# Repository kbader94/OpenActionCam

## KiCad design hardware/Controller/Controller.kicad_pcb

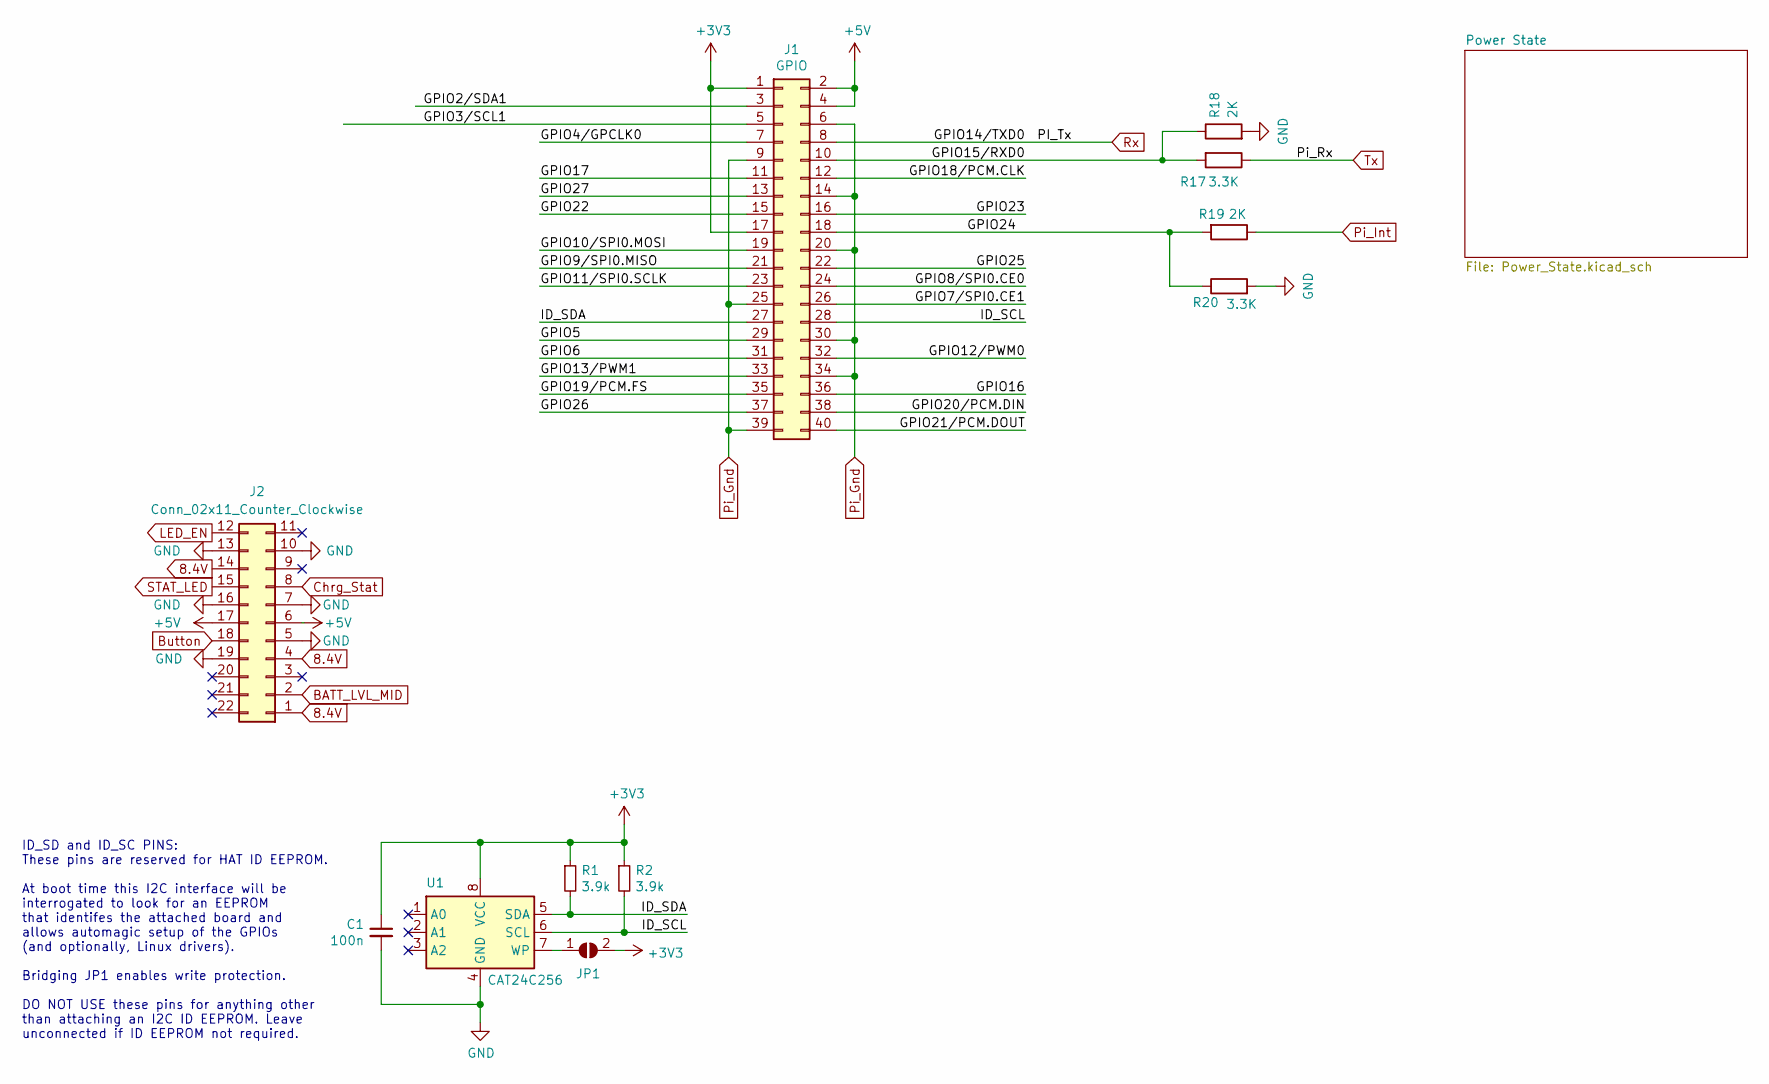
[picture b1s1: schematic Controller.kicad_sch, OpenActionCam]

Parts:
C1: 100n; C_0603_1608Metric_Pad1.08x0.95mm_HandSolder
J1: GPIO; Raspberry_Pi_Zero_Socketed_THT_FaceDown_MountingHoles
J2: Conn_02x11_Counter_Clockwise; Board_outline
JP1: ID_WP; SolderJumper-2_P1.3mm_Open_Pad1.0x1.5mm
R1, R2: 3.9k; R_0603_1608Metric_Pad0.98x0.95mm_HandSolder
R17, R20: 3.3K; R_0603_1608Metric_Pad0.98x0.95mm_HandSolder
R18, R19: 2K; R_0603_1608Metric_Pad0.98x0.95mm_HandSolder
U1: CAT24C256; SOIC127P600X175-8N

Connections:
8.4V: J2.1, J2.4, J2.14; also elsewhere on the board
+3V3: C1.1, J1.1, J1.17, JP1.2 (B), R1.1, R2.1, U1.8 (VCC)
+5V: J1.2, J1.4, J2.6, J2.17; also elsewhere on the board
/GPIO2/SDA1: J1.3
/GPIO3/SCL1: J1.5
/GPIO4/GPCLK0: J1.7
/GPIO5: J1.29
/GPIO6: J1.31
/GPIO7/SPI0.CE1: J1.26
/GPIO8/SPI0.CE0: J1.24
/GPIO9/SPI0.MISO: J1.21
/GPIO10/SPI0.MOSI: J1.19
/GPIO11/SPI0.SCLK: J1.23
/GPIO12/PWM0: J1.32
/GPIO13/PWM1: J1.33
/GPIO15/RXD0: J1.10, R17.2, R18.1
/GPIO16: J1.36
/GPIO17: J1.11
/GPIO18/PCM.CLK: J1.12
/GPIO19/PCM.FS: J1.35
/GPIO20/PCM.DIN: J1.38
/GPIO21/PCM.DOUT: J1.40
/GPIO22: J1.15
/GPIO23: J1.16
/GPIO24: J1.18, R19.1, R20.2
/GPIO25: J1.22
/GPIO26: J1.37
/GPIO27: J1.13
/ID_SCL: J1.28, R2.2, U1.6 (SCL)
/ID_SDA: J1.27, R1.2, U1.5 (SDA)
BATT_LVL_MID: J2.2; also elsewhere on the board
Button: J2.18; also elsewhere on the board
Chrg_Stat: J2.8; also elsewhere on the board
GND: C1.2, J2.5, J2.7, J2.10, J2.13, J2.16, J2.19, R18.2, R19.2, U1.4 (GND); also elsewhere on the board
LED_EN: J2.12; also elsewhere on the board
unnamed: JP1.1 (A), U1.7 (WP)
Pi_Gnd: J1.6, J1.9, J1.14, J1.20, J1.25, J1.30, J1.34, J1.39; also elsewhere on the board
Pi_Int: R20.1; also elsewhere on the board
Rx: J1.8; also elsewhere on the board
STAT_LED: J2.15; also elsewhere on the board
Tx: R17.1; also elsewhere on the board

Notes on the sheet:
ID_SD and ID_SC PINS: These pins are reserved for HAT ID EEPROM. At boot time this I2C interface will be interrogated to look for an EEPROM that identifes the attached board and allows automagic setup of the GPIOs (and optionally, Linux drivers). Bridging JP1 enables write protection. DO NOT USE th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

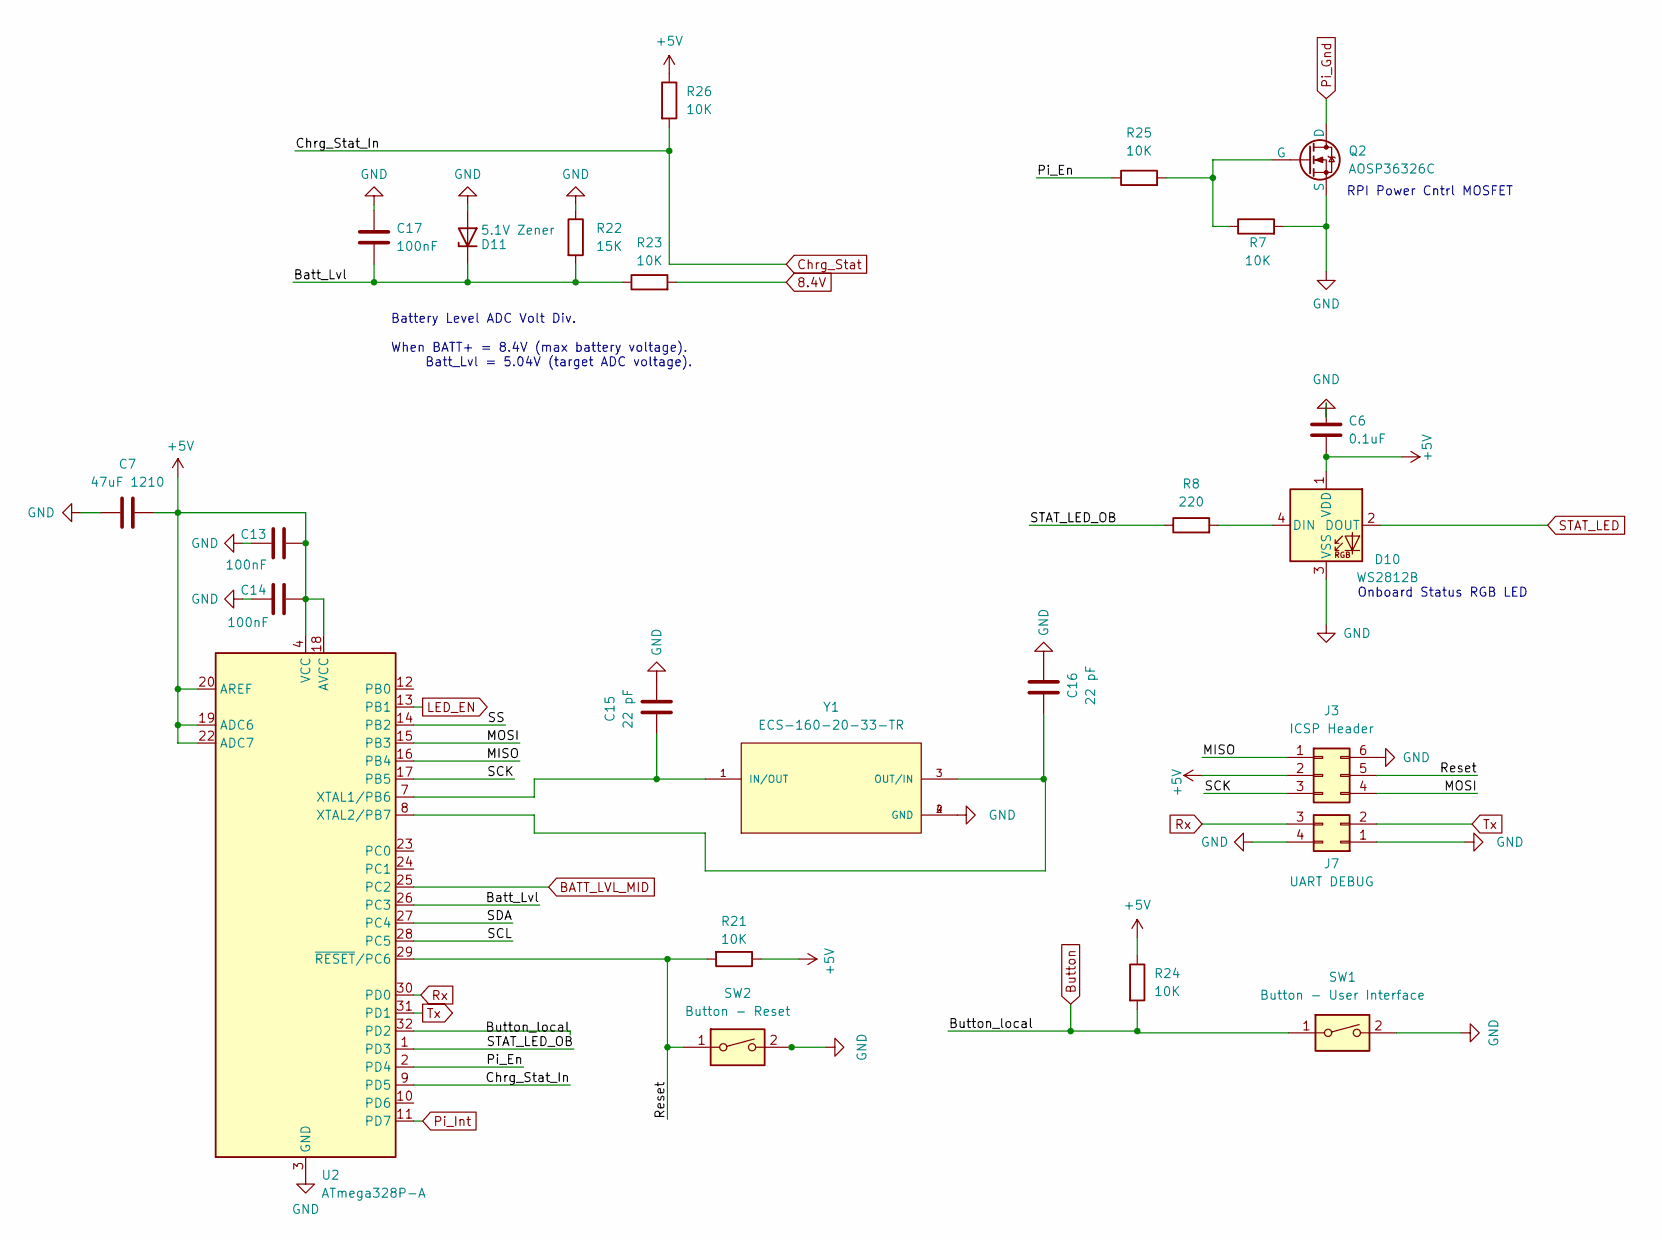
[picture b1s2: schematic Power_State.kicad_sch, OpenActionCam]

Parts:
C6: 0.1uF; C_0603_1608Metric_Pad1.08x0.95mm_HandSolder
C7: 47uF 1210; C_1210_3225Metric_Pad1.33x2.70mm_HandSolder
C13, C14, C17: 100nF; C_0603_1608Metric_Pad1.08x0.95mm_HandSolder
C15, C16: 22 pF; C_0603_1608Metric_Pad1.08x0.95mm_HandSolder
D10: WS2812B; LED_WS2812B_PLCC4_5.0x5.0mm_P3.2mm
D11: 5.1V Zener; D_SOD-323_HandSoldering
J3: ICSP Header; PinSocket_2x03_P2.54mm_Vertical
J7: UART DEBUG; PinSocket_2x02_P2.54mm_Vertical
Q2: AOSP36326C; SOIC127P490X600X175-8N
R7, R21, R23, R24: 10K; R_0603_1608Metric_Pad0.98x0.95mm_HandSolder
R8: 220; R_0603_1608Metric_Pad0.98x0.95mm_HandSolder
R22: 15K; R_0603_1608Metric_Pad0.98x0.95mm_HandSolder
R25, R26: 10K; R_0603_1608Metric
SW1: Button - User Interface; SW4_PTS815 SJM 250 SMTR LFS_CNK
SW2: Button - Reset; SW4_PTS815 SJM 250 SMTR LFS_CNK
U2: ATmega328P-A; TQFP-32_7x7mm_P0.8mm
Y1: ECS-160-20-33-TR; XTAL_ECS-160-20-33-TR

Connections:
8.4V: R23.2; also elsewhere on the board
+5V: C6.2, C7.2, C13.2, C14.2, D10.1 (VDD), J3.2, R21.1, R24.1, R26.1, U2.4 (VCC), U2.6 (VCC), U2.18 (AVCC), U2.19 (ADC6), U2.20 (AREF), U2.22 (ADC7); also elsewhere on the board
/Power State/Batt_Lvl: C17.2, D11.1 (K), R22.2, R23.1, U2.26 (PC3)
/Power State/MISO: J3.1, U2.16 (PB4)
/Power State/MOSI: J3.4, U2.15 (PB3)
/Power State/Pi_En: R25.1, U2.2 (PD4)
/Power State/Reset: J3.5, R21.2, SW2.1, U2.29 (~RESET/PC6)
/Power State/SCK: J3.3, U2.17 (PB5)
/Power State/SCL: U2.28 (PC5)
/Power State/SDA: U2.27 (PC4)
/Power State/SS: U2.14 (PB2)
/Power State/STAT_LED_OB: R8.1, U2.1 (PD3)
BATT_LVL_MID: U2.25 (PC2); also elsewhere on the board
Button: R24.2, SW1.1, U2.32 (PD2); also elsewhere on the board
Chrg_Stat: R26.2, U2.9 (PD5); also elsewhere on the board
GND: C6.1, C7.1, C13.1, C14.1, C15.2, C16.2, C17.1, D10.3 (VSS), D11.2 (A), J3.6, J7.1, J7.4, Q2.3 (S), R7.2, R22.1, SW1.2, SW2.2, U2.3 (GND), U2.5 (GND), U2.21 (GND), Y1.2 (GND), Y1.4 (GND); also elsewhere on the board
LED_EN: U2.13 (PB1); also elsewhere on the board
unnamed: D10.4 (DIN), R8.2
unnamed: Q2.2 (G), R7.1, R25.2
unnamed: C15.1, U2.7 (XTAL1/PB6), Y1.1 (IN/OUT)
unnamed: C16.1, U2.8 (XTAL2/PB7), Y1.3 (OUT/IN)
Pi_Gnd: Q2.1 (D); also elsewhere on the board
Pi_Int: U2.11 (PD7); also elsewhere on the board
Rx: J7.3, U2.30 (PD0); also elsewhere on the board
STAT_LED: D10.2 (DOUT); also elsewhere on the board
Tx: J7.2, U2.31 (PD1); also elsewhere on the board

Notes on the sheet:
Onboard Status RGB LED
RPI Power Cntrl MOSFET
Battery Level ADC Volt Div. When BATT+ = 8.4V (max battery voltage). Batt_Lvl = 5.04V (target ADC voltage).

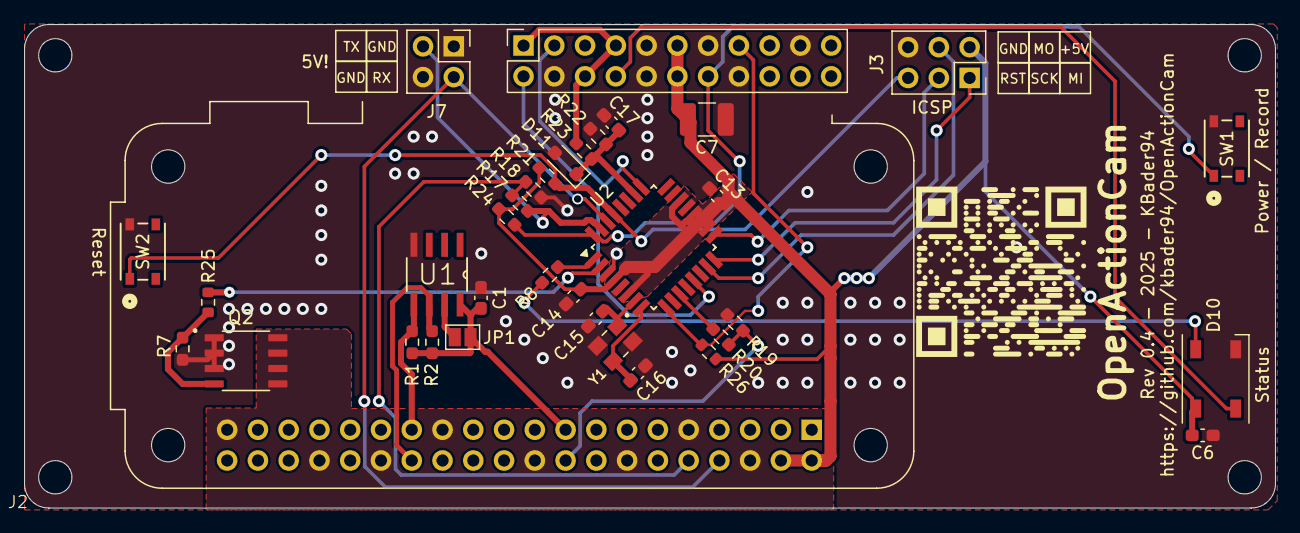
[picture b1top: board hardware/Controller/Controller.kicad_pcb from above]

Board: 2 copper layers, 103.3 x 39.9 mm, 35 parts (1 on the bottom side), 29 nets.

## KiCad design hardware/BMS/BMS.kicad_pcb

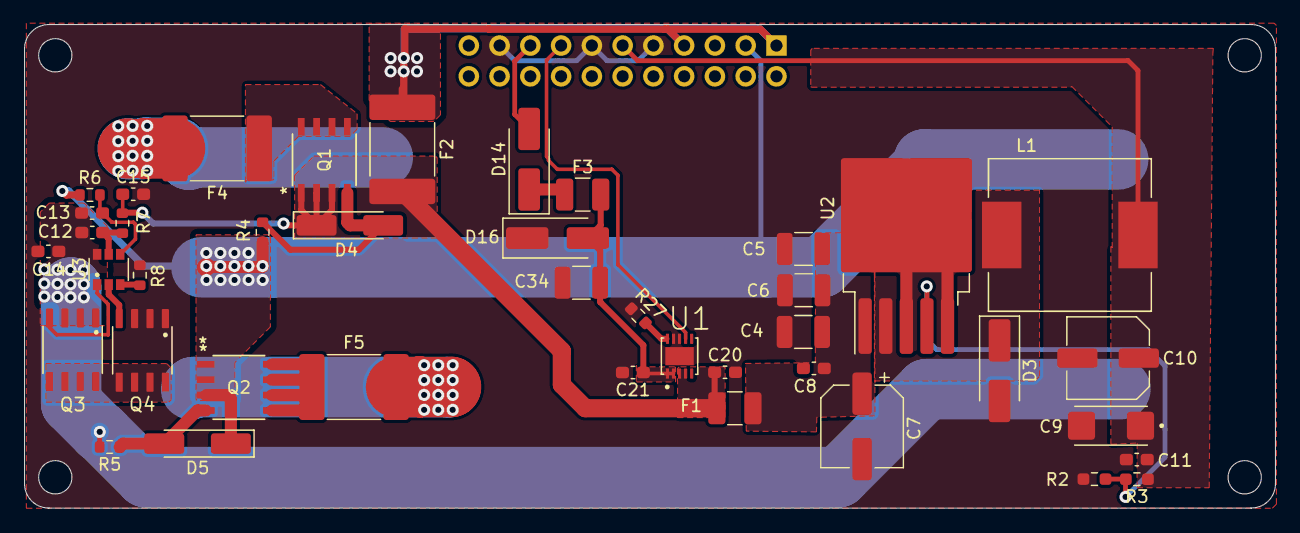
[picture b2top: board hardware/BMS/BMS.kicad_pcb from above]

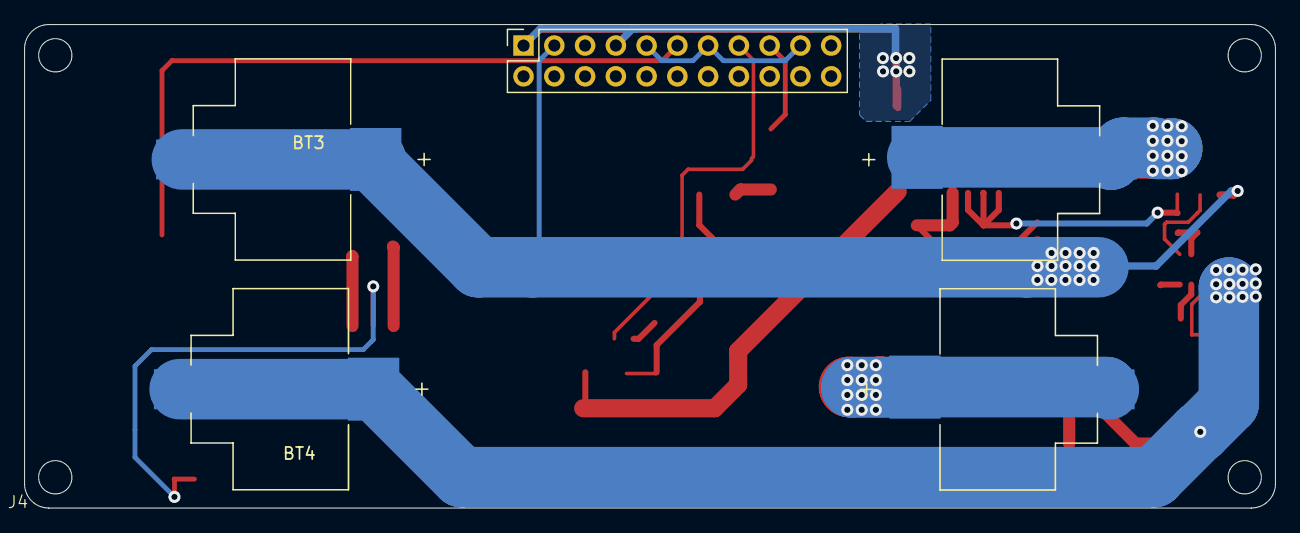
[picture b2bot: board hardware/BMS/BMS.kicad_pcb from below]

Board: 2 copper layers, 103.3 x 39.9 mm, 44 parts (3 on the bottom side), 26 nets.

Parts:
BT3, BT4: Battery_Cell; BAT_254
C4, C5, C6, C34: 47uF; R_1210_3225Metric_Pad1.30x2.65mm_HandSolder
C7: 100uF 16V; CP_Elec_6.3x7.7
C8, C11, C12, C14, C15: 0.1uF; C_0603_1608Metric_Pad1.08x0.95mm_HandSolder
C9: 330uF Tantalum; CAPPM6032X280N
C10: 330uF 10V; C_Elec_6.3x7.7
C13: 0.1 uF; C_0603_1608Metric_Pad1.08x0.95mm_HandSolder
C20, C21: 10uF; C_0603_1608Metric_Pad1.08x0.95mm_HandSolder
D3: SS34; D_SMA_Handsoldering
D4, D5: 9.1V Zener; D_MiniMELF_Handsoldering
D14: SS24; D_SMA_Handsoldering
D16: SMAJ11A; D_SMA_Handsoldering
F1, F3: 2.2A Polyfuse; Fuse_1210_3225Metric_Pad1.42x2.65mm_HandSolder
F2: 6A Polyfuse; Fuse_2920_7451Metric_Pad2.10x5.45mm_HandSolder
F4, F5: Polyfuse 6A; Fuse_2920_7451Metric_Pad2.10x5.45mm_HandSolder
J4: Conn_01x11; Board_outline
L1: 33uH; IND_125CDMCCDS-330MC
Q1, Q2: SI4435FDY; SO-8_VIS
Q3, Q4: AOSP36326C; SOIC127P490X600X175-8N
R2: 1K; R_0603_1608Metric_Pad0.98x0.95mm_HandSolder
R3: 3.1K; R_0603_1608Metric_Pad0.98x0.95mm_HandSolder
R4, R5: 100K; R_0603_1608Metric
R6, R7: 330; R_0603_1608Metric
R8: 2.2K; R_0603_1608Metric
R27: 1K; R_0603_1608Metric
U1: MCP73213-A6SI_MF; SON50P300X300X100-11N
U2: LM2596S-ADJ; TO-263-5_TabPin3
U3: MM3220AA2NRH; IC_MM3220AA2NRH

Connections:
8.4V: C15.1, C20.1, D4.1 (K), F1.1, F2.2, Q1.3 (S), R7.2, U1.3 (VBAT), U1.4 (VBAT)
+5V: C9.1, C10.1, C11.1, J4.6, L1.2, R3.1
+12V: C21.1, C34.2, D16.2 (A2), F3.2, U1.1 (VDD), U1.2 (VDD)
/Power BMS/8.4V Out: F2.1, J4.1, J4.4
/Power BMS/Battery Pack & Protection/8.4unsafe: F4.1, Q1.1 (D)
/Power BMS/Battery Pack & Protection/d2d: Q3.1 (D), Q4.1 (D)
/Power BMS/Power Supply/V_Out_Dirty: D3.1 (K), L1.1, U2.2 (OUT)
/Power BMS/Power Supply/Vin_clean: C4.1, C5.1, C6.1, C7.1, C8.1, F1.2, U2.1 (VIN)
BATT_LVL-: BT4.2 (-), C12.1, C13.2, C14.2, Q3.3 (S), R5.2, U3.6 (VSS)
BATT_LVL_MID: BT3.2 (-), D5.1 (K), J4.2, Q2.3 (S), R4.2, R6.1
Chrg_Stat: J4.8, U1.7 (STAT)
GND: C4.2, C5.2, C6.2, C7.2, C8.2, C9.2, C10.2, C11.2, C14.1, C15.2, C20.2, C21.2, C34.1, D3.2 (A), D16.1 (A1), J4.5, J4.7, J4.10, Q4.3 (S), R2.1, R8.2, R27.1, U1.8 (VSS), U1.9 (VSS), U1.11 (EP), U2.3 (GND), U2.5 (~ON/OFF)
unnamed: BT3.1 (+), F4.2
unnamed: BT4.1 (+), F5.2
unnamed: D4.2 (A), Q1.2 (G), R4.1
unnamed: D5.2 (A), Q2.2 (G), R5.1
unnamed: D14.2 (A), J4.9
unnamed: D14.1 (K), F3.1
unnamed: F5.1, Q2.1 (D)
unnamed: Q3.2 (G), U3.1 (DOUT)
unnamed: Q4.2 (G), U3.2 (COUT)
unnamed: R27.2, U1.10 (PROG)
unnamed: R2.2, R3.2, U2.4 (FB)
unnamed: R8.1, U3.3 (V-)
unnamed: C13.1, R6.2, U3.4 (VBL)
unnamed: C12.2, R7.1, U3.5 (VDD)

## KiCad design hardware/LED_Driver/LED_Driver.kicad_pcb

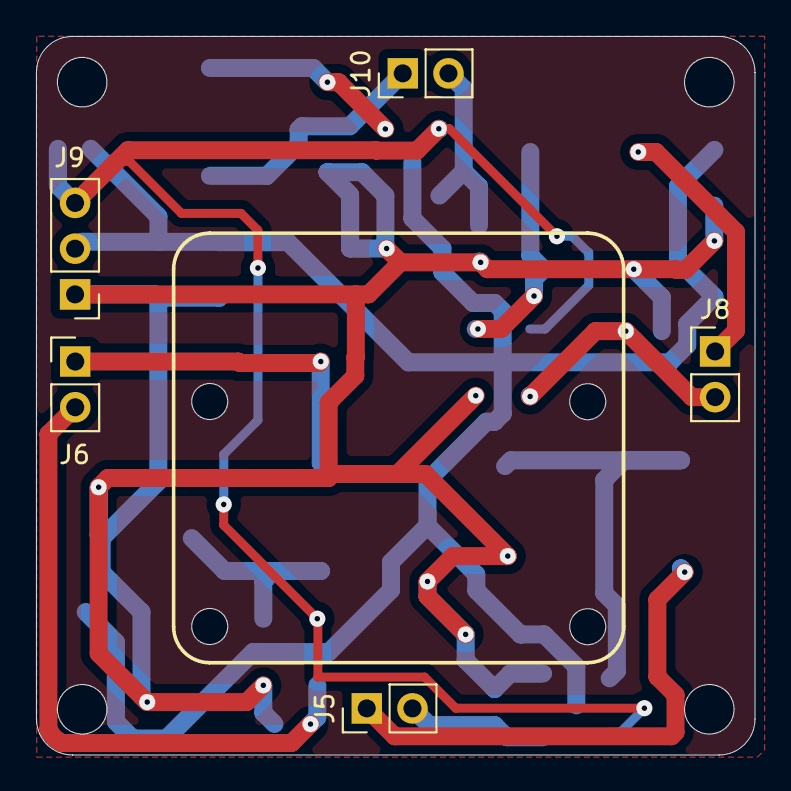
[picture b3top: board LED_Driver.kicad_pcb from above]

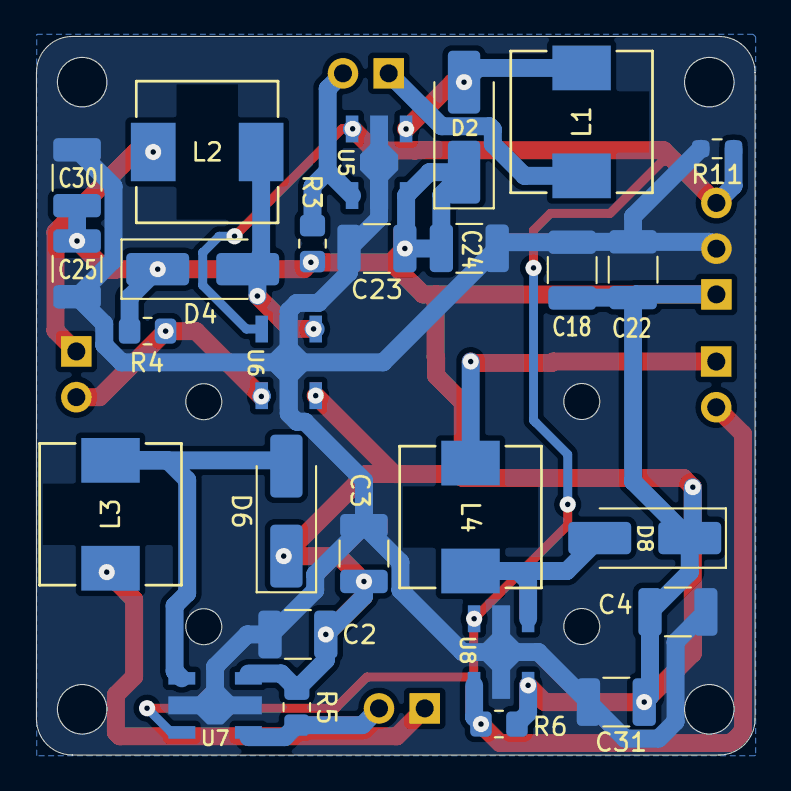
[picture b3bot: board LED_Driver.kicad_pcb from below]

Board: 2 copper layers, 39.9 x 39.9 mm, 32 parts (27 on the bottom side), 15 nets.

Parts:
C2, C3, C4, C18, C22, C23, C24, C25, C30, C31: 47uF 1210; R_1210_3225Metric_Pad1.30x2.65mm_HandSolder
D2, D4, D6, D8: SS14; D_SMA_Handsoldering
J5, J8, J9, J10: Conn_01x02_Pin; PinHeader_1x02_P2.54mm_Vertical
J6: Conn_01x03; PinHeader_1x03_P2.54mm_Vertical
L1, L2, L3, L4: 68 uH; DR74
R3: 0.15 - 0805; R_0805_2012Metric_Pad1.20x1.40mm_HandSolder
R4: 0.15 -0805; R_0805_2012Metric_Pad1.20x1.40mm_HandSolder
R5, R6: 0.15; R_0805_2012Metric_Pad1.20x1.40mm_HandSolder
R11: 10K; R_0603_1608Metric_Pad0.98x0.95mm_HandSolder
U5, U6, U7, U8: PT4115; SOT-89-5

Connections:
8.4V: C2.1, C3.1, C4.1, C18.1, C22.1, C23.1, C24.1, C25.1, C30.1, C31.1, D2.1 (K), D4.1 (K), D6.1 (K), D8.1 (K), J6.1, R3.1, R4.1, R5.1, R6.1, U5.5 (VIN), U6.5 (VIN), U7.5 (VIN), U8.5 (VIN)
GND: C2.2, C3.2, C4.2, C18.2, C22.2, C23.2, C24.2, C25.2, C30.2, C31.2, J6.2, R11.2, U5.2 (GND), U6.2 (GND), U7.2 (GND), U8.2 (GND)
LED_EN: J6.3, R11.1, U5.3 (DIM), U6.3 (DIM), U7.3 (DIM), U8.3 (DIM)
unnamed: D2.2 (A), L1.2, U5.1 (SW)
unnamed: D4.2 (A), L2.2, U6.1 (SW)
unnamed: D6.2 (A), L3.2, U7.1 (SW)
unnamed: D8.2 (A), L4.2, U8.1 (SW)
unnamed: J5.1, L3.1
unnamed: J5.2, R5.2, U7.4 (CSN)
unnamed: J8.1, L2.1
unnamed: J8.2, R4.2, U6.4 (CSN)
unnamed: J9.1, L4.1
unnamed: J9.2, R6.2, U8.4 (CSN)
unnamed: J10.1, L1.1
unnamed: J10.2, R3.2, U5.4 (CSN)

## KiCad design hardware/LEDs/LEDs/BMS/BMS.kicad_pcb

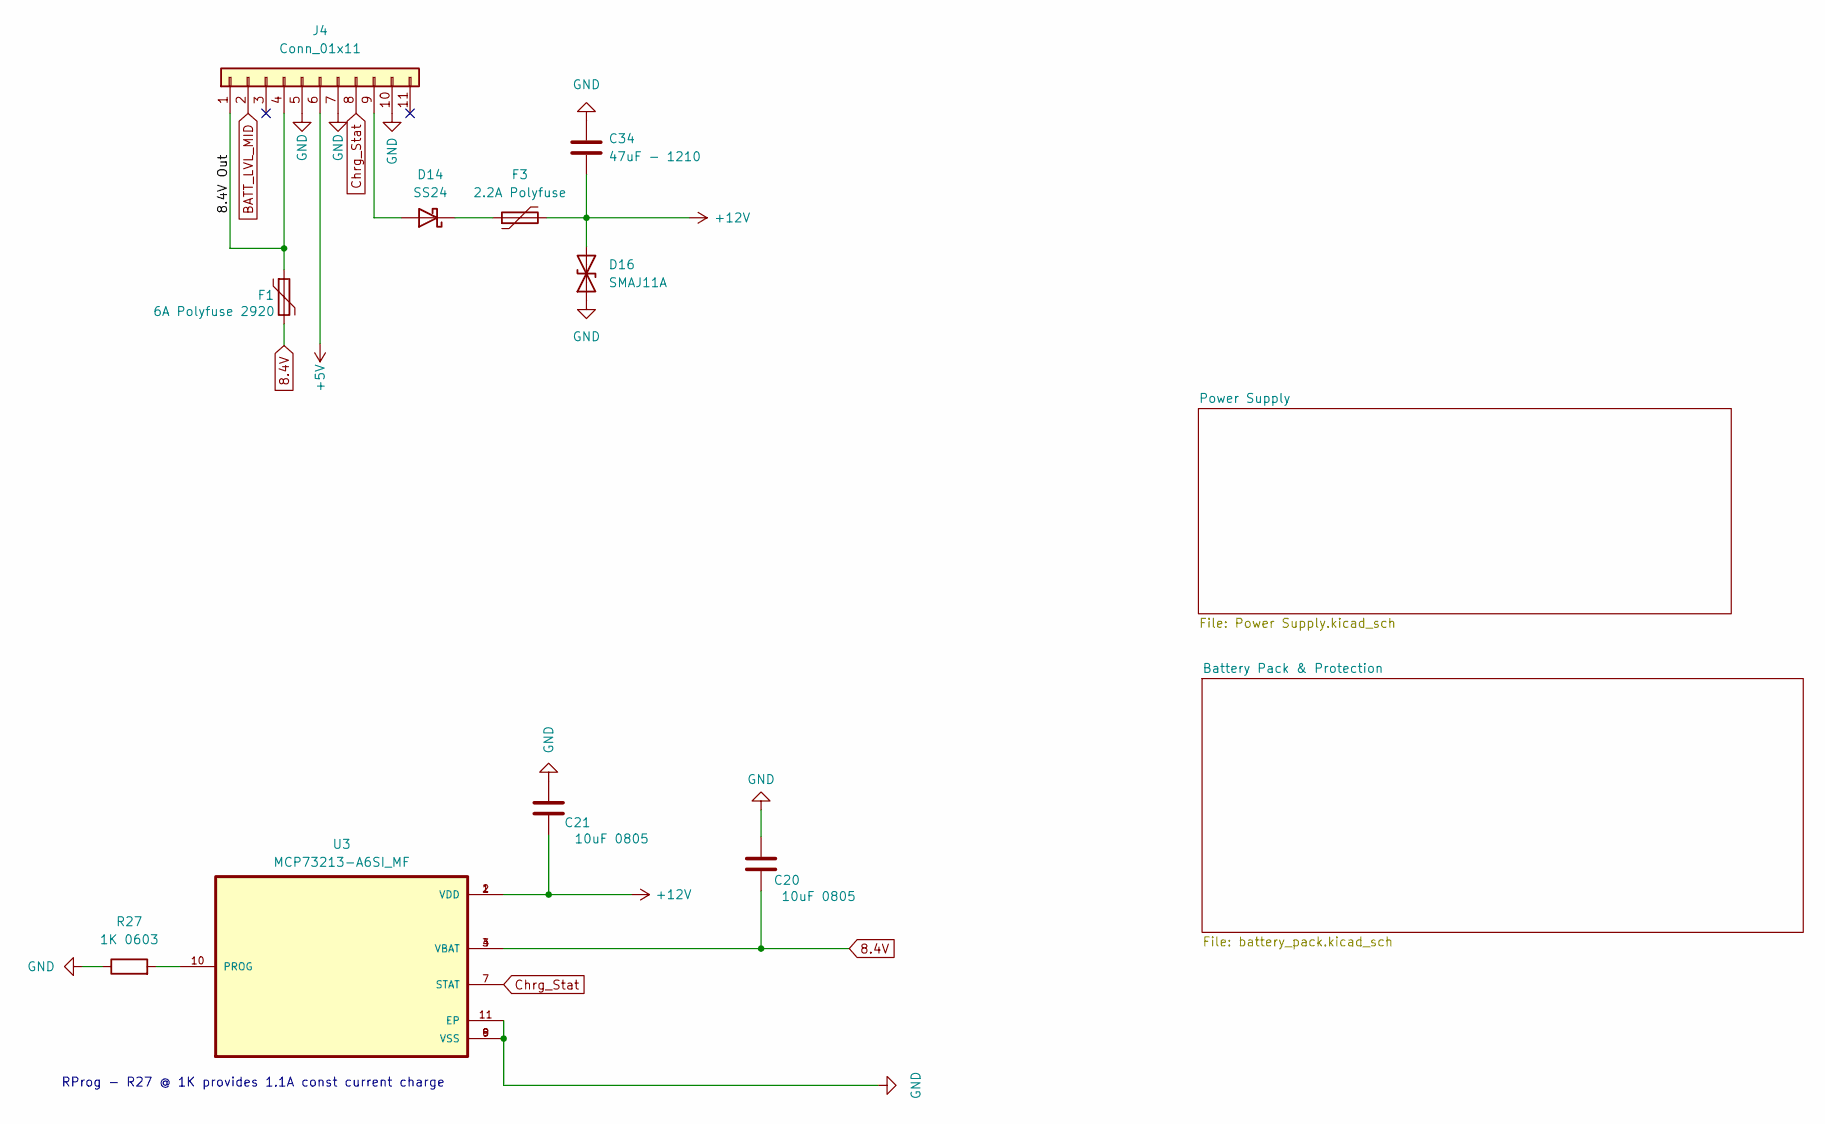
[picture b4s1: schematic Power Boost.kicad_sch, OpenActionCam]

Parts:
C20, C21: 10uF 0805; C_0603_1608Metric_Pad1.08x0.95mm_HandSolder
C34: 47uF - 1210; R_1210_3225Metric_Pad1.30x2.65mm_HandSolder
D14: SS24; D_SMA_Handsoldering
D16: SMAJ11A; D_SMA_Handsoldering
F1: 6A Polyfuse 2920; Fuse_2920_7451Metric_Pad2.10x5.45mm_HandSolder
F3: 2.2A Polyfuse; Fuse_1210_3225Metric_Pad1.42x2.65mm_HandSolder
J4: Conn_01x11; Board_outline
R27: 1K 0603; R_0603_1608Metric
U3: MCP73213-A6SI_MF; SON50P300X300X100-11N

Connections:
8.4V: C20.1, F1.2, U3.3 (VBAT), U3.4 (VBAT); also elsewhere on the board
+5V: J4.6; also elsewhere on the board
+12V: C21.1, C34.2, D16.2 (A2), F3.2, U3.1 (VDD), U3.2 (VDD)
/Power BMS/8.4V Out: F1.1, J4.1, J4.4
BATT_LVL_MID: J4.2; also elsewhere on the board
Chrg_Stat: J4.8, U3.7 (STAT)
GND: C20.2, C21.2, C34.1, D16.1 (A1), J4.5, J4.7, J4.10, R27.1, U3.8 (VSS), U3.9 (VSS), U3.11 (EP); also elsewhere on the board
unnamed: D14.2 (A), J4.9
unnamed: D14.1 (K), F3.1
unnamed: R27.2, U3.10 (PROG)

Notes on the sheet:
RProg - R27 @ 1K provides 1.1A const current charge

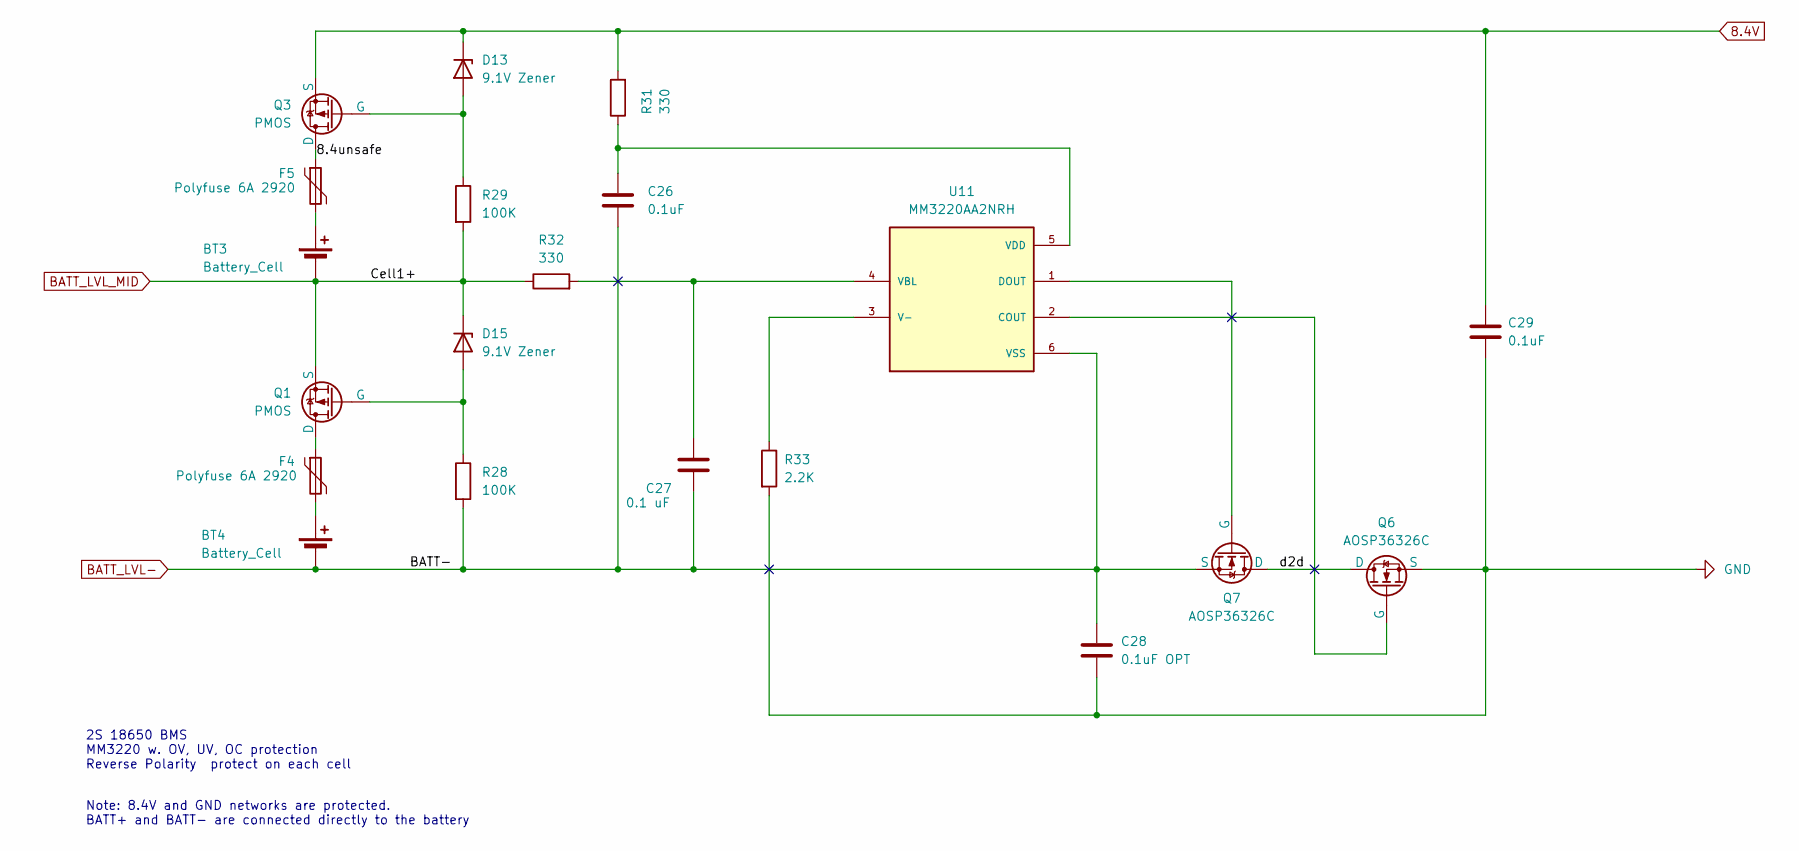
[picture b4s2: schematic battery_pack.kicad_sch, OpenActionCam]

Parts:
BT3, BT4: Battery_Cell; BAT_254
C26, C29: 0.1uF; C_0603_1608Metric_Pad1.08x0.95mm_HandSolder
C27: 0.1 uF; C_0603_1608Metric_Pad1.08x0.95mm_HandSolder
C28: 0.1uF OPT; C_0603_1608Metric_Pad1.08x0.95mm_HandSolder
D13, D15: 9.1V Zener; D_MiniMELF_Handsoldering
F4, F5: Polyfuse 6A 2920; Fuse_2920_7451Metric_Pad2.10x5.45mm_HandSolder
Q1, Q3: PMOS; SO-8_VIS
Q6, Q7: AOSP36326C; SOIC127P490X600X175-8N
R28, R29: 100K; R_0603_1608Metric
R31, R32: 330; R_0603_1608Metric
R33: 2.2K; R_0603_1608Metric
U11: MM3220AA2NRH; IC_MM3220AA2NRH; PARTREV 0

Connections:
8.4V: C29.1, D13.1 (K), Q3.3 (S), R31.2; also elsewhere on the board
/Power BMS/Battery Pack & Protection/8.4unsafe: F5.1, Q3.1 (D)
/Power BMS/Battery Pack & Protection/d2d: Q6.1 (D), Q7.1 (D)
BATT_LVL-: BT4.2 (-), C26.1, C27.2, C28.2, Q7.3 (S), R28.2, U11.6 (VSS)
BATT_LVL_MID: BT3.2 (-), D15.1 (K), Q1.3 (S), R29.2, R32.1; also elsewhere on the board
GND: C28.1, C29.2, Q6.3 (S), R33.2; also elsewhere on the board
unnamed: BT3.1 (+), F5.2
unnamed: BT4.1 (+), F4.2
unnamed: D13.2 (A), Q3.2 (G), R29.1
unnamed: D15.2 (A), Q1.2 (G), R28.1
unnamed: F4.1, Q1.1 (D)
unnamed: Q6.2 (G), U11.2 (COUT)
unnamed: Q7.2 (G), U11.1 (DOUT)
unnamed: R33.1, U11.3 (V-)
unnamed: C27.1, R32.2, U11.4 (VBL)
unnamed: C26.2, R31.1, U11.5 (VDD)

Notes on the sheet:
2S 18650 BMS MM3220 w. OV, UV, OC protection Reverse Polarity protect on each cell
Note: 8.4V and GND networks are protected. BATT+ and BATT- are connected directly to the battery

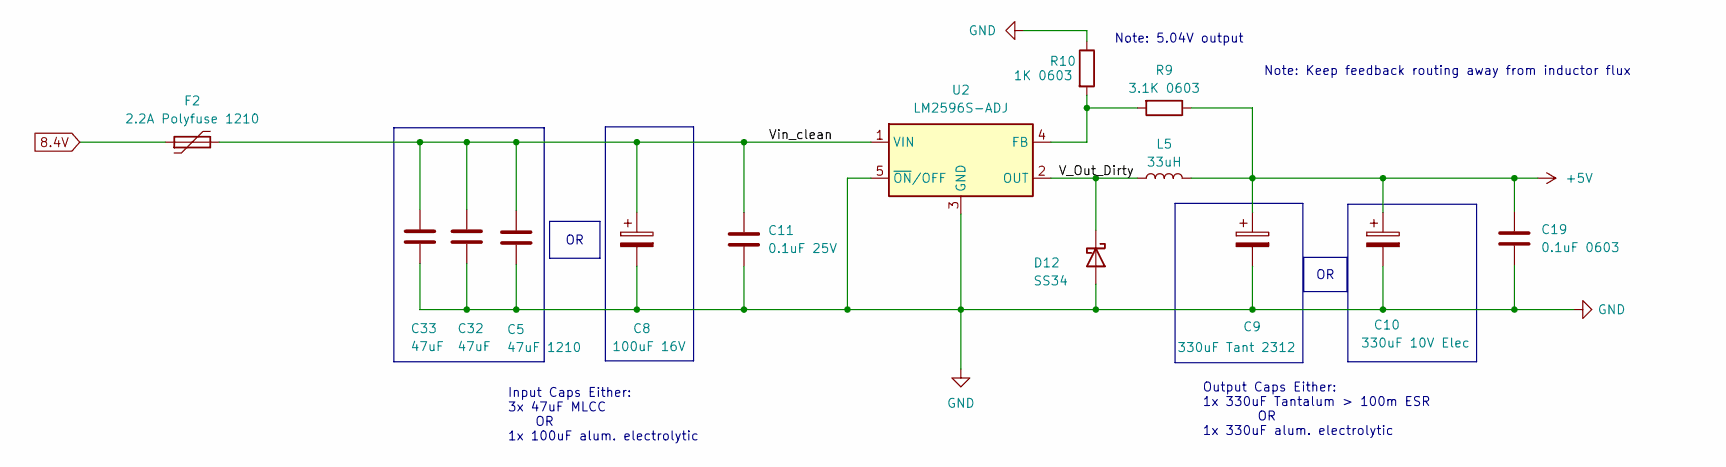
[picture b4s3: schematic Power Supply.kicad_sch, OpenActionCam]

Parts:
C5: 47uF 1210; R_1210_3225Metric_Pad1.30x2.65mm_HandSolder
C8: 100uF 16V; CP_Elec_6.3x7.7
C9: 330uF Tant 2312; CAPPM6032X280N
C10: 330uF 10V Elec; C_Elec_6.3x7.7
C11: 0.1uF 25V; C_0603_1608Metric_Pad1.08x0.95mm_HandSolder
C19: 0.1uF 0603; C_0603_1608Metric_Pad1.08x0.95mm_HandSolder
C32, C33: 47uF; R_1210_3225Metric_Pad1.30x2.65mm_HandSolder
D12: SS34; D_SMA_Handsoldering
F2: 2.2A Polyfuse 1210; Fuse_1210_3225Metric_Pad1.42x2.65mm_HandSolder
L5: 33uH; IND_125CDMCCDS-330MC
R9: 3.1K 0603; R_0603_1608Metric_Pad0.98x0.95mm_HandSolder
R10: 1K 0603; R_0603_1608Metric_Pad0.98x0.95mm_HandSolder
U2: LM2596S-ADJ; TO-263-5_TabPin3

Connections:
8.4V: F2.1; also elsewhere on the board
+5V: C9.1, C10.1, C19.1, L5.2, R9.1; also elsewhere on the board
/Power BMS/Power Supply/V_Out_Dirty: D12.1 (K), L5.1, U2.2 (OUT)
/Power BMS/Power Supply/Vin_clean: C5.1, C8.1, C11.1, C32.1, C33.1, F2.2, U2.1 (VIN)
GND: C5.2, C8.2, C9.2, C10.2, C11.2, C19.2, C32.2, C33.2, D12.2 (A), R10.1, U2.3 (GND), U2.5 (~ON/OFF); also elsewhere on the board
unnamed: R9.2, R10.2, U2.4 (FB)

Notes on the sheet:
Note: 5.04V output
Input Caps Either: 3x 47uF MLCC OR 1x 100uF alum. electrolytic
Output Caps Either: 1x 330uF Tantalum > 100m ESR OR 1x 330uF alum. electrolytic
Note: Keep feedback routing away from inductor flux

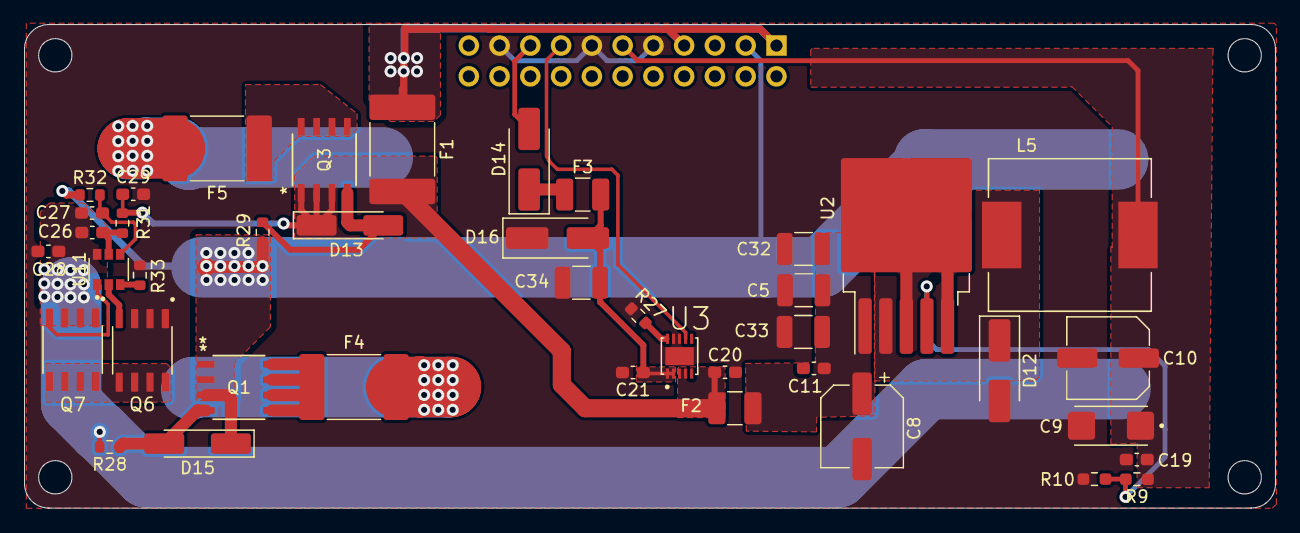
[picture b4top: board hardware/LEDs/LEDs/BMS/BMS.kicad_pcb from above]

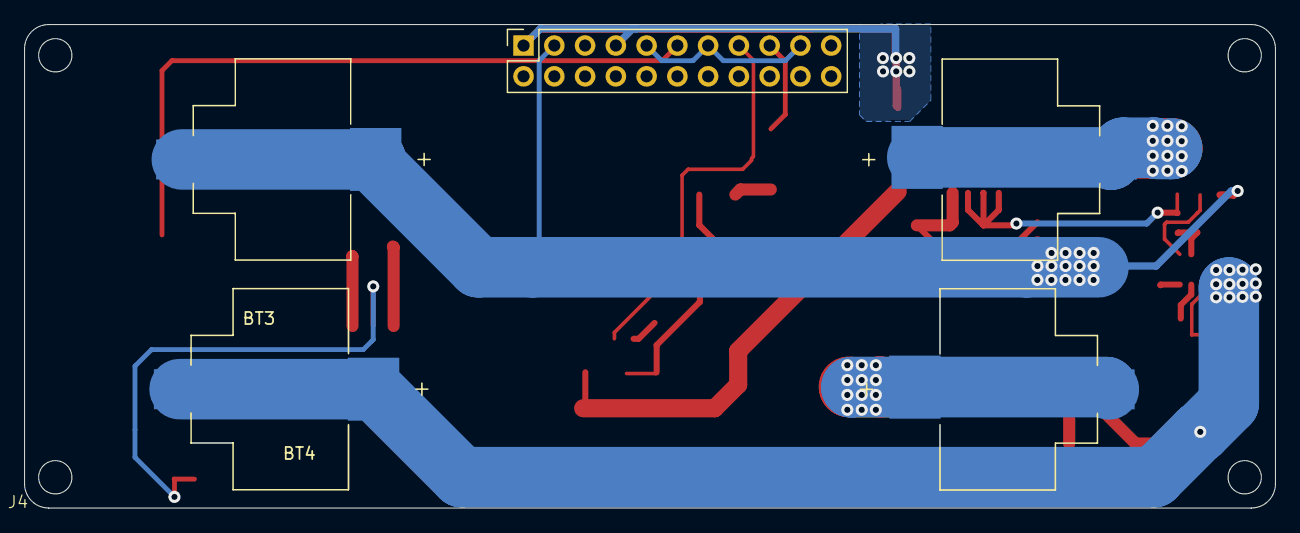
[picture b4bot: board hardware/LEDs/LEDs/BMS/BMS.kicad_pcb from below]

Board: 2 copper layers, 103.3 x 39.9 mm, 44 parts (3 on the bottom side), 26 nets.

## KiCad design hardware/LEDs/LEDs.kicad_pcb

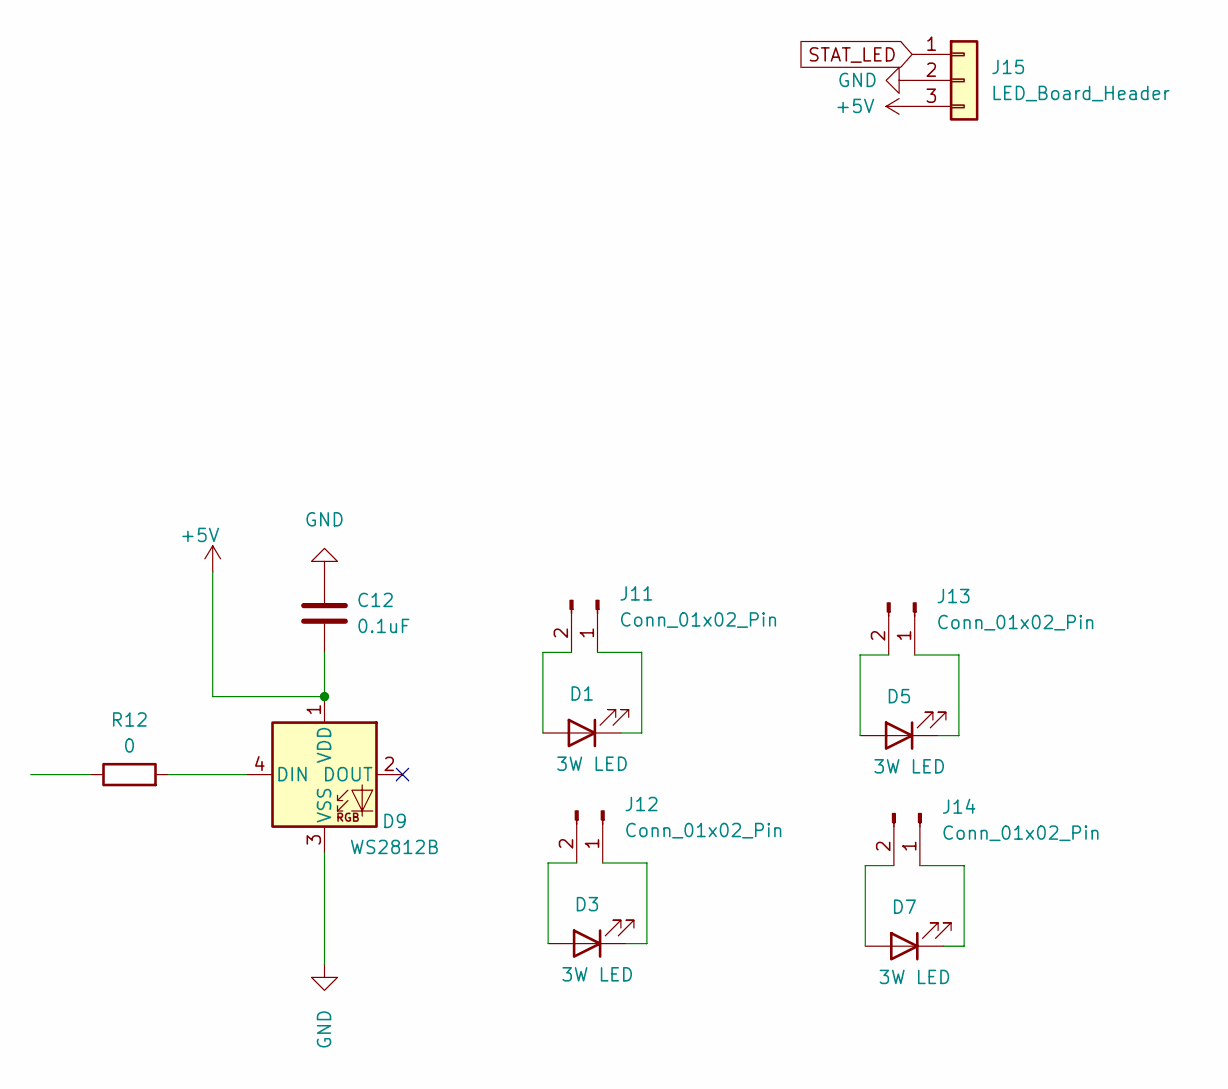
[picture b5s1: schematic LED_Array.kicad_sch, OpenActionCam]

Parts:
C12: 0.1uF; C_0603_1608Metric_Pad1.08x0.95mm_HandSolder
D1, D3, D5, D7: 3W LED; BEAD-3W-W-120-04
D9: WS2812B; LED_WS2812B_PLCC4_5.0x5.0mm_P3.2mm
J11, J12, J13, J14: Conn_01x02_Pin; PinHeader_1x02_P2.54mm_Vertical
J15: LED_Board_Header; PinHeader_1x03_P2.54mm_Vertical
R12: 0; R_0603_1608Metric_Pad0.98x0.95mm_HandSolder

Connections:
+5V: C12.2, D9.1 (VDD), J15.3
GND: C12.1, D9.3 (VSS), J15.2
unnamed: D1.2 (A), J11.2
unnamed: D1.1 (K), J11.1
unnamed: D3.2 (A), J12.2
unnamed: D3.1 (K), J12.1
unnamed: D5.2 (A), J13.2
unnamed: D5.1 (K), J13.1
unnamed: D7.2 (A), J14.2
unnamed: D7.1 (K), J14.1
unnamed: D9.4 (DIN), R12.2
STAT_LED: J15.1
